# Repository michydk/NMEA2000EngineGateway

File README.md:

# NMEA2000EngineGateway

Basicly an non invasive way to messure oil and coolingwater temperature along with RPM on altenator, and then report result via NMEA 2000 to plotter.

Based on the shoulders of my hero's, including but not limited to:

DallasTemperature: Miles Burton https://github.com/milesburton

NMEA2000: Timo Lappalainen https://github.com/ttlappalainen

OneWire: Paul Stoffregen https://github.com/PaulStoffregen

More info can be found on my blog https://sillydiy.blogspot.com/2022/01/measuring-boat-engine-temperature-wih.html

# PCB
PCB production: https://aisler.net/p/SUMPWCYW 
Schems etc. is included in the "Arduino_RPM_Shield" folder

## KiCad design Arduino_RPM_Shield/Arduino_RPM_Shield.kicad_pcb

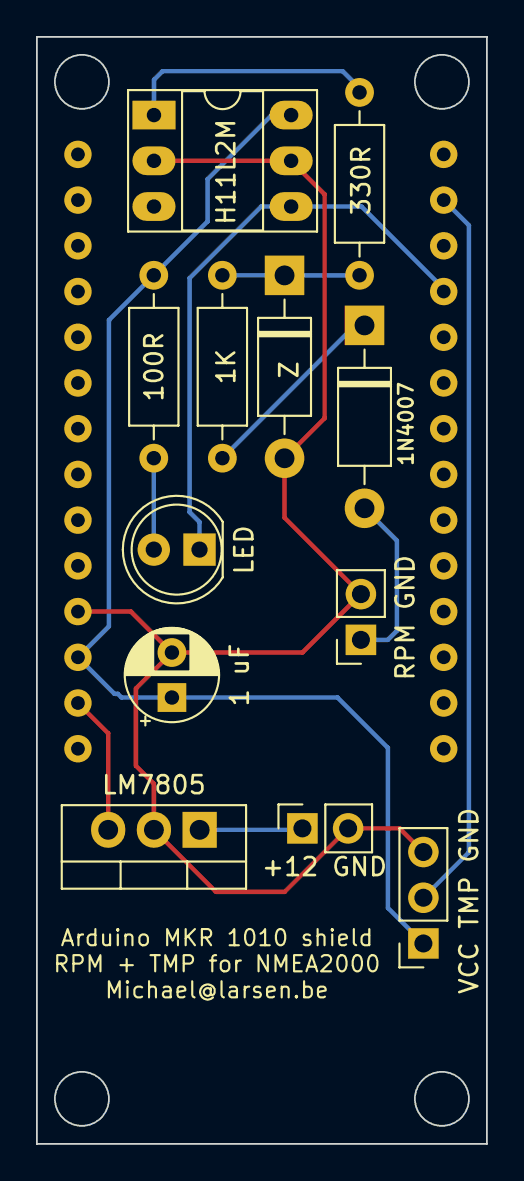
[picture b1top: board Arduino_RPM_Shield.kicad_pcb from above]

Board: 2 copper layers, 25.0 x 61.5 mm, 13 parts (0 on the bottom side), 11 nets.

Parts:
C1: 1 uF; CP_Radial_D5.0mm_P2.50mm
D1: 1N4007; D_DO-41_SOD81_P10.16mm_Horizontal
D2: 1N4732A; D_DO-41_SOD81_P10.16mm_Horizontal
D3: LED; LED_D5.0mm
J1: RPM GND; PinSocket_1x02_P2.54mm_Vertical
J3: +12 GND; PinSocket_1x02_P2.54mm_Vertical
J4: VCC TMP GND; PinSocket_1x03_P2.54mm_Vertical
MKR1: Arduino_MKR_Shield; Arduino_MKR
R1: 1K; R_Axial_DIN0207_L6.3mm_D2.5mm_P10.16mm_Horizontal
R2: 330R; R_Axial_DIN0207_L6.3mm_D2.5mm_P10.16mm_Horizontal
R3: 100R; R_Axial_DIN0207_L6.3mm_D2.5mm_P10.16mm_Horizontal
U1: H11L2M; DIP-6_W7.62mm_Socket_LongPads
U2: LM7805; TO-220-3_Vertical

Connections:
+12V: J3.1, U2.1 (VI)
GND: C1.2, D2.2 (A), J1.2, J3.2, J4.3, MKR1.25 (GND), U1.2, U1.5, U2.2 (GND)
unnamed: C1.1, J4.1, MKR1.26 (3V3), R3.1, U1.6
unnamed: D1.1 (K), R1.1
unnamed: D2.1 (K), R1.2, R2.1
unnamed: D3.1 (K), MKR1.11 (D2), U1.4
unnamed: D3.2 (A), R3.2
unnamed: J4.2, MKR1.13 (D4)
unnamed: MKR1.27 (Vin), U2.3 (VO)
unnamed: R2.2, U1.1
Tacho IN: D1.2 (A), J1.1

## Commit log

2022-02-07 Init PCB ver 1.0
2022-02-07 init ino file
2022-02-07 Update README.md
    Added link for PCB production
